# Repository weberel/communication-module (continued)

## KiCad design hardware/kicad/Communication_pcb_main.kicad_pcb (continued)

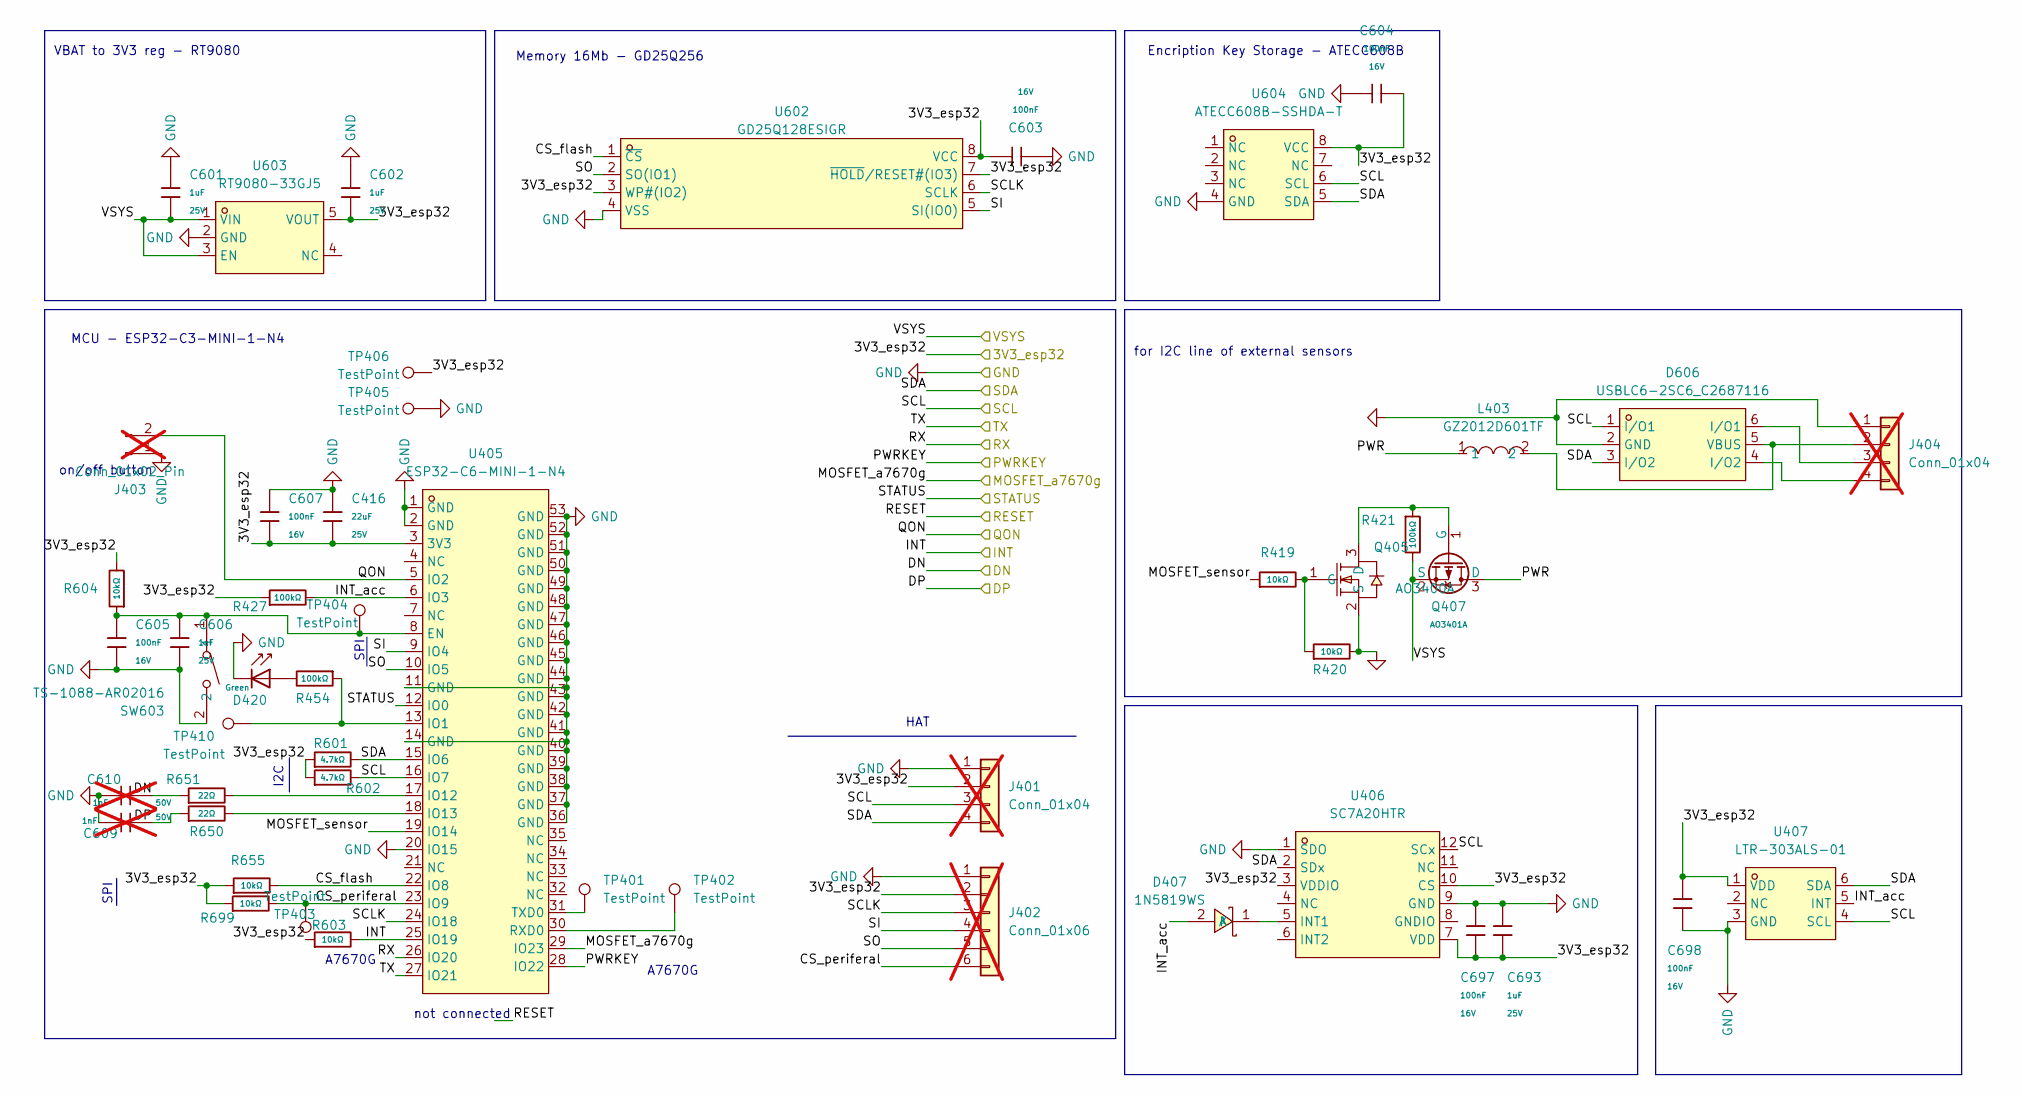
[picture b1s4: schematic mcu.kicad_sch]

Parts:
C416: 22uF; C_0805; Voltage Rated 25V; Tolerance ±20%; Part CL21A226MAQNNNE; LCSC C45783
C601, C602, C606, C693: 1uF; C_0402; Voltage Rated 25V; Tolerance ±10%; Part CL05A105KA5NQNC; LCSC C52923
C603, C604, C605, C607, C697, C698: 100nF; C_0402; Voltage Rated 16V; Tolerance ±10%; Part CL05B104KO5NNNC; LCSC C1525
C609, C610: 1nF; C_0402; Voltage Rated 50V; Tolerance ±10%; Part 0402B102K500NT; LCSC C1523; not fitted
D407: 1N5819WS; SOD-323_L1.8-W1.3-LS2.5-RD; MPN 1N5819WS; LCSC Part C191023
D420: Green; D_0805; Part KT-0805G; LCSC C2297
D606: USBLC6-2SC6_C2687116; SOT-23-6_L2.9-W1.6-P0.95-LS2.8-BL; LCSC Part C2687116
J401, J404: Conn_01x04; custom_01x04_2.54; not fitted
J402: Conn_01x06; custom_01x06_2.54; not fitted
J403: Conn_01x02_Pin; custom_1x02_2.54; not fitted
L403: GZ2012D601TF; L0805; MPN GZ2012D601TF; LCSC Part C1017
Q405: AO3400A; SOT-23-3_L2.9-W1.3-P1.90-LS2.4-BR; MPN AO3400A; LCSC Part C20917
Q407: AO3401A; Q_SOT-23; Part AO3401A; LCSC C15127
R419, R420, R603, R604, R655, R699: 10kΩ; R_0402; Overload Voltage (Max) 50V; Tolerance ±1%; Part 0402WGF1002TCE; LCSC C25744
R421, R427, R454: 100kΩ; R_0402; Overload Voltage (Max) 50V; Tolerance ±1%; Part 0402WGF1003TCE; LCSC C25741
R601, R602: 4.7kΩ; R_0402; Overload Voltage (Max) 50V; Tolerance ±1%; Part 0402WGF4701TCE; LCSC C25900
R650, R651: 22Ω; R_0402; Overload Voltage (Max) 50V; Tolerance ±1%; Part 0402WGF220JTCE; LCSC C25092
SW603: TS-1088-AR02016; SW-SMD_L3.9-W3.0-P4.45; LCSC Part C720477
TP401, TP402, TP403, TP404, TP405, TP406, TP410: TestPoint; TestPoint_Pad_D1.0mm
U405: ESP32-C6-MINI-1-N4; WIFIM-SMD_61P-L16.6-W13.2-P0.80-ESP32-C6-MINI-1-N4; LCSC Part C5736265
U406: SC7A20HTR; LGA-12_L2.0-W2.0-P0.50-TL; MPN SC7A20HTR; LCSC Part C19274408
U407: LTR-303ALS-01; TDFN-6_L2.0-W2.0-P0.65-BL; MPN LTR-303ALS-01; LCSC Part C364577
U602: GD25Q128ESIGR; SOP-8_L5.3-W5.3-P1.27-LS8.0-BL; LCSC Part C2928891
U603: RT9080-33GJ5; TSOT-23-5_L2.9-W1.6-P0.95-LS2.8-BL; LCSC Part C841192
U604: ATECC608B-SSHDA-T; SOIC-8_L4.9-W3.9-P1.27-LS6.0-BL; LCSC Part C1518769

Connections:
/MCU/3V3_esp32: C416.2, C602.2, C603.2, C604.2, C607.1, C693.2, C697.1, C698.2, J401.2, J402.2, R427.1, R601.1, R602.1, R603.1, R604.2, R655.1, R699.1, TP406.1 (1_1), U405.3 (3V3), U406.3 (VDDIO), U406.7 (VDD), U406.10 (CS), U407.1 (VDD), U602.3 (WP#(IO2)), U602.7 (~HOLD/RESET#(IO3)), U602.8 (VCC), U603.5 (VOUT), U604.8 (VCC); also elsewhere on the board
/MCU/CS_flash: R655.2, U405.22 (IO8), U602.1 (~CS)
/MCU/CS_periferal: J402.6, R699.2, TP403.1 (1_1), U405.23 (IO9)
/MCU/DN: C610.2, R651.1; also elsewhere on the board
/MCU/DP: C609.2, R650.1; also elsewhere on the board
/MCU/INT: R603.2, U405.25 (IO19); also elsewhere on the board
/MCU/INT_acc: D407.2 (A), R427.2, U405.6 (IO3), U407.5 (INT)
/MCU/MOSFET_a7670g: U405.29 (IO23); also elsewhere on the board
/MCU/MOSFET_sensor: R419.1, U405.19 (IO14)
/MCU/PWR: L403.1, Q407.3 (D)
/MCU/PWRKEY: U405.28 (IO22); also elsewhere on the board
/MCU/QON: J403.2, U405.5 (IO2); also elsewhere on the board
/MCU/RX: U405.26 (IO20); also elsewhere on the board
/MCU/SCL: D606.1 (I/O1), J401.3, R602.2, U405.16 (IO7), U406.12 (SCx), U407.4 (SCL), U604.6 (SCL); also elsewhere on the board
/MCU/SCLK: J402.3, U405.24 (IO18), U602.6 (SCLK)
/MCU/SDA: D606.3 (I/O2), J401.4, R601.2, U405.15 (IO6), U406.2 (SDx), U407.6 (SDA), U604.5 (SDA); also elsewhere on the board
/MCU/SI: J402.4, U405.9 (IO4), U602.5 (SI(IO0))
/MCU/SO: J402.5, U405.10 (IO5), U602.2 (SO(IO1))
/MCU/STATUS: U405.12 (IO0); also elsewhere on the board
/MCU/TX: U405.27 (IO21); also elsewhere on the board
/MCU/VSYS: C601.2, Q407.2 (S), R421.2, U603.1 (VIN), U603.3 (EN); also elsewhere on the board
GND: C416.1, C601.1, C602.1, C603.1, C604.1, C605.1, C606.2, C607.2, C609.1, C610.1, C693.1, C697.2, C698.1, D420.1, D606.2 (GND), J401.1, J402.1, J403.1, J404.1, Q405.2 (S), R420.2, SW603.2, TP405.1 (1_1), U405.1 (GND), U405.2 (GND), U405.11 (GND), U405.14 (GND), U405.20 (IO15), U405.36 (GND), U405.37 (GND), U405.38 (GND), U405.39 (GND), U405.40 (GND), U405.41 (GND), U405.42 (GND), U405.43 (GND), U405.44 (GND), U405.45 (GND), U405.46 (GND), U405.47 (GND), U405.48 (GND), U405.49 (GND), U405.50 (GND), U405.51 (GND), U405.52 (GND), U405.53 (GND), U406.1 (SDO), U406.9 (GND), U407.3 (GND), U602.4 (VSS), U603.2 (GND), U604.4 (GND); also elsewhere on the board
unnamed: D407.1 (K), U406.5 (INT1)
unnamed: D420.2, R454.2
unnamed: D606.5 (VBUS), J404.2, L403.2
unnamed: D606.6 (I/O1), J404.3
unnamed: D606.4 (I/O2), J404.4
unnamed: Q405.3 (D), Q407.1 (G), R421.1
unnamed: Q405.1 (G), R419.2, R420.1
unnamed: C605.2, C606.1, R604.1, SW603.1, TP404.1 (1_1), U405.8 (EN)
unnamed: R454.1, TP410.1 (1_1), U405.13 (IO1)
unnamed: R651.2, U405.17 (IO12)
unnamed: R650.2, U405.18 (IO13)
unnamed: TP402.1 (1_1), U405.30 (RXD0)
unnamed: TP401.1 (1_1), U405.31 (TXD0)

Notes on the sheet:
SPI
I2C
VBAT to 3V3 reg - RT9080
HAT
for I2C line of external sensors
A7670G
Memory 16Mb - GD25Q256
not connected
MCU - ESP32-C3-MINI-1-N4
on/off button
Encription Key Storage - ATECC608B

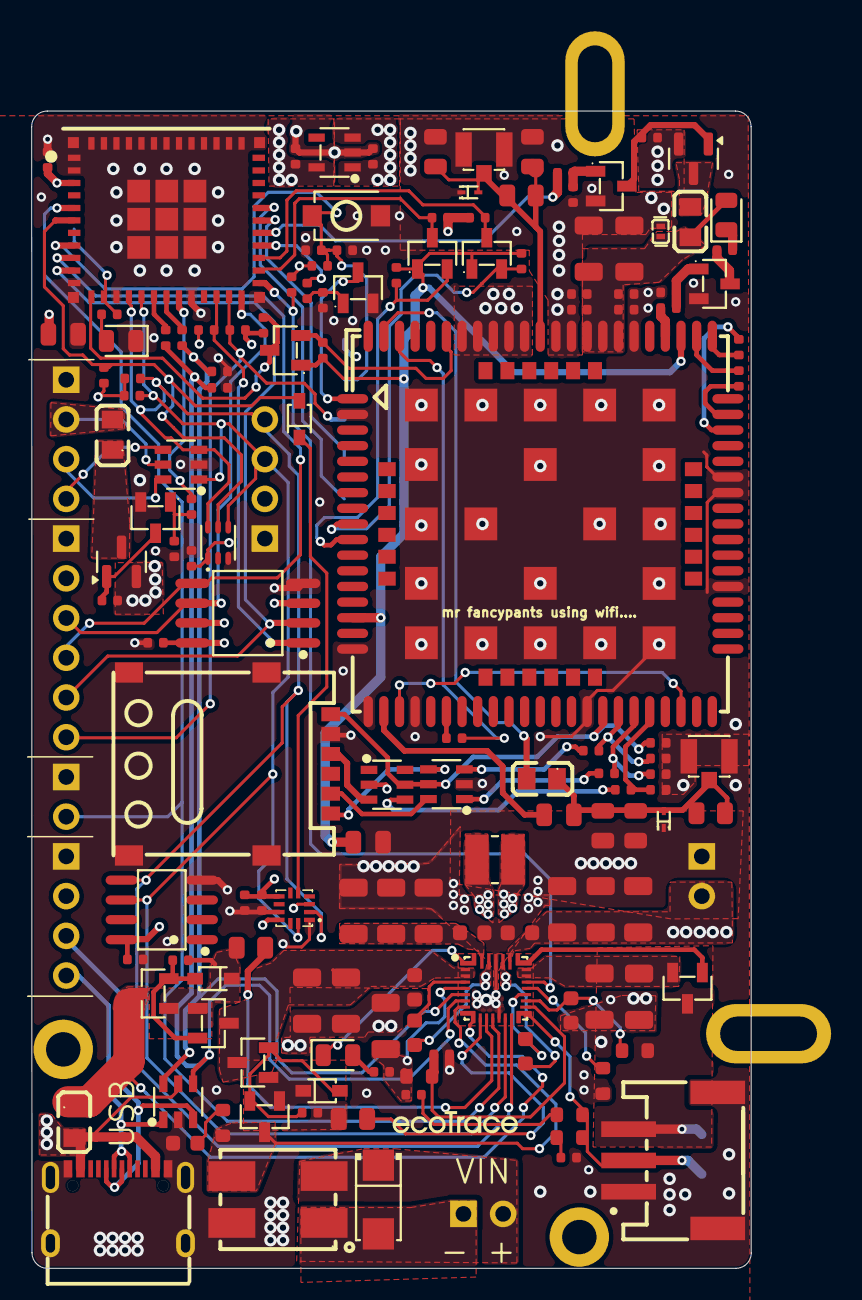
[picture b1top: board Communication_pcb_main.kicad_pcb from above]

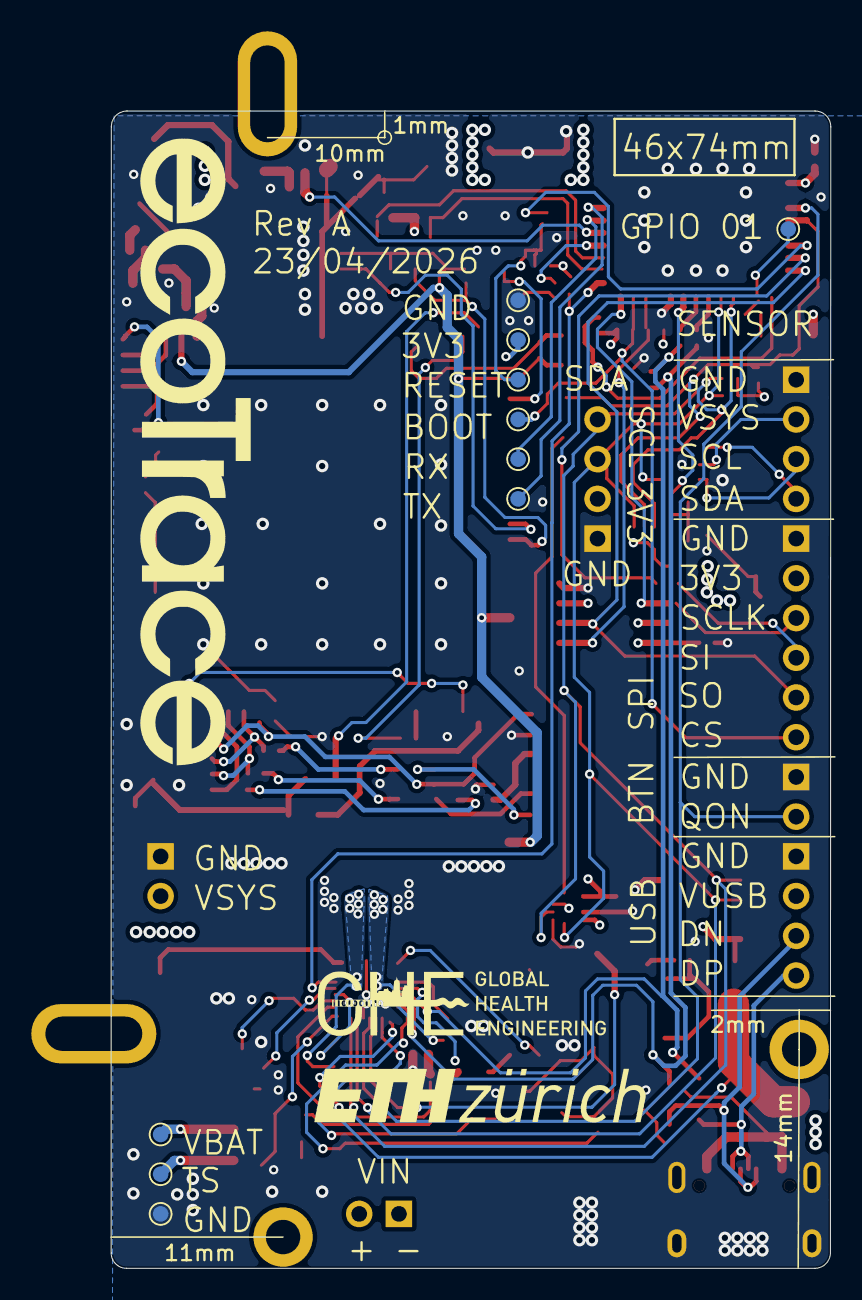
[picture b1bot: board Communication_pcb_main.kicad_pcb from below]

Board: 4 copper layers, 46.0 x 74.0 mm, 165 parts (10 on the bottom side), 102 nets.

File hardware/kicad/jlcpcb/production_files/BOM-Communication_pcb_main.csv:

Comment,Designator,Footprint,LCSC,Quantity
100kΩ,"R201,R209,R418,R421,R427,R454",R_0402,C25741,6
100nF,"C202,C206,C217",C_0603,C14663,3
100nF,"C402,C409,C603,C604,C605,C607,C697,C698",C_0402,C1525,8
100pF,C418,C_0805,C1790,1
100Ω,R208,R_0603,C22775,1
10kΩ,"R403,R404,R405,R406,R407,R408,R415,R416,R417,R419,R420,R422,R423,R603,R604,R655,R699",R_0402,C25744,17
10pF,C404,C_0402,C32949,1
10uF,"C203,C204,C205,C207,C209,C210,C211,C212,C218,C219",C_1206,C13585,10
150kΩ,R223,R_0603,C22807,1
1N5819WS,D407,SOD-323_L1.8-W1.3-LS2.5-RD,C191023,1
1kΩ,"R402,R413,R414",R_0402,C11702,3
1nF,"C220,C221",C_0402,C1523,2
1uF,C417,C_0603,C15849,1
1uF,"C411,C601,C602,C606,C693",C_0402,C52923,5
2.2uF,C415,C_0805,C377773,1
2.2Ω,R424,R_0603,C22939,1
220kΩ,R212,R_0603,C22961,1
22pF,"C406,C407,C408",C_0402,C1555,3
22uF,C416,C_0805,C45783,1
22Ω,"R409,R410,R411,R650,R651",R_0402,C25092,5
27kΩ,R224,R_0603,C22967,1
3.3kΩ,R225,R_0402,C25890,1
300Ω,"R213,R214",R_0805,C17617,2
33pF,C403,C_0402,C1562,1
3kΩ,R202,R_0603,C4211,1
4.7kΩ,"R425,R601,R602",R_0402,C25900,3
4.7uF,C201,C_1206,C29823,1
47kΩ,R426,R_0402,C25792,1
47nF,"C208,C213,C214",C_0603,C1622,3
47uF,"C401,C410",C_1206,C96123,2
5.1kΩ,R222,R_0402,C25905,1
A7672E (LASE),U403,LGA-124_L24.0-W24.0-P1.0-A7670C-LASS,C6116733,1
AO3400A,"Q201,Q202,Q203,Q204,Q206,Q401,Q402,Q403,Q405,Q406,Q408,Q409",SOT-23-3_L2.9-W1.3-P1.90-LS2.4-BR,C20917,12
AO3401A,"Q404,Q407",Q_SOT-23,C15127,2
ATECC608B-SSHDA-T,U604,SOIC-8_L4.9-W3.9-P1.27-LS6.0-BL,C1518769,1
BQ25792RQMR,U202,QFN-29_L4.0-W4.0-P0.40-TL-BQ25792RQMR,C2862876,1
BZT52C9V1S,"D203,D204",SOD-323_L1.8-W1.3-LS2.5-RD,C22614,2
ESD9X3.3ST5G,"D403,D406",SOD-923_L0.8-W0.6-LS1.0-RD,C130456,2
ESDBW5V0A1_C5173252,U404,X1-DFN1006-2_L1.0-W0.6-P0.65-BI,C5173252,1
ESP32-C6-MINI-1-N4,U405,WIFIM-SMD_61P-L16.6-W13.2-P0.80-ESP32-C6-MINI-1-N4,C5736265,1
GD25Q128ESIGR,U602,SOP-8_L5.3-W5.3-P1.27-LS8.0-BL,C2928891,1
GZ2012D601TF,"L403,L404",L0805,C1017,2
Green,"D201,D402,D420",D_0805,C2297,3
LTR-303ALS-01,U407,TDFN-6_L2.0-W2.0-P0.65-BL,C364577,1
MPZ2012S221AT000,"L401,L402",L0805,C76818,2
RSCM7060-701,L407,FILTER-SMD_4P-L7.0-W6.0-P3.00-TL,C32712963,1
RT9080-33GJ5,U603,TSOT-23-5_L2.9-W1.6-P0.95-LS2.8-BL,C841192,1
SC7A20HTR,U406,LGA-12_L2.0-W2.0-P0.50-TL,C19274408,1
SMAJ30A,D401,SMA_L4.3-W2.6-LS5.2-RD,C10767,1
SMN-303,Card401,SIM-SMD_SMN-305,C266890,1
TS-1088-AR02016,SW603,SW-SMD_L3.9-W3.0-P4.45,C720477,1
TYPE-C 16PIN 2MD(073),J201,USB-C-SMD_TYPE-C-6PIN-2MD-073,C2765186,1
USBLC6-2SC6_C2687116,"D212,D404,D405,D606",SOT-23-6_L2.9-W1.6-P0.95-LS2.8-BL,C2687116,4
VLS3012HBX-1R0M,L201,IND-SMD_L3.0-W3.0_VLS3012CX,C404493,1
WAFER-PH2.0-3PWB,J202,CONN-SMD_3P-P2.00_XUNPU_WAFER-PH2.0-3PWB,C3029441,1
ZX-RF-1-Z21.25X,"U401,U402",IPEX-SMD_3P-L2.6-W2.6-LS3.0_YUANDI_RF-001,C7426714,2
